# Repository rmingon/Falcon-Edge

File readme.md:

# FALCON-EDGE — An Open-Source Flying-Wing with an ESP32 Flight Computer

This repository contains hardware designs, documentation, and code for an aircraft project.

### New light version 400g instead of 800g

Falcon-Edge is a compact flying-wing airframe with a custom **ESP32-based flight computer**.  
This repo contains the **KiCad hardware project** and **3D CAD** needed to print, assemble, and fly your own Falcon-Edge.

---

## Highlights

- **Airframe**

  - 3D-printable center pod with **top and bottom service hatches** for fast access.
  - Designed for clean airflow over the pod; embedded antenna keep-out zone.
  - Uses off-the-shelf wing cores/foam or your own prints.

- **Avionics (KiCad)**
  - **ESP32-WROOM** module as the main controller (Wi-Fi/BLE for ground testing & logs).
  - **IMU:** MPU-6050 6-axis.
  - **Baro:** BMP280.
  - **GNSS header** for a u-blox NEO-style GPS module.
  - **Power:** AMS1117 regulators (3V3/5V) and dedicated servo power planes/decoupling.
  - **Programming:** UART header with EN/BOOT auto-reset circuitry.
  - **RF/Telemetry:** LoRa with edge SMA/U.FL footprint for an external antenna.

> See the schematic for exact pin mapping and connector naming.

---

## 📂 Repository Layout

hardware/ # KiCad project (.kicad_pro, .kicad_pcb, .kicad_sch, etc.)
cad/ # 3D parts for the center pod, hatches, and mounting (STLs/STEP)
images/ # Renders and board views used in this README (optional)

(If you keep everything at the repo root, this README references the images there by filename.)

---

## 🛠️ Getting Started

### 1) Hardware (KiCad)

- Open with **KiCad 8.x** or newer.
- Files:
  - `hardware.kicad_pro` – project
  - `hardware.kicad_sch` – schematic
  - `hardware.kicad_pcb` – PCB layout
- Generate Gerbers/BoM as usual and order from your preferred fab.

**Board preview**

**Schematic overview**

### 2) Print & Fit the Pod

- Recommended: **PETG** or **ABS** for the pod & hatches (heat-tolerant in the sun).
- Use heat-set **M3 inserts** for the hatch screws and board standoffs.
- Verify antenna **keep-out** in the pod before final mounting.

**Top hatch opening**

**Bottom hatch opening**

### 3) Wiring (at a glance)

- **Battery in** → power/battery header near regulators.
- **GPS** → dedicated UART header / GPS footprint.
- **Programming** → UART (EN/BOOT accessible).
- **Telemetry/Radio** → SMA/U.FL at the board edge.

> Exact connector names/positions: see the KiCad schematic & silkscreen.

---

## 📸 Gallery

**3D view of the board**

**Airframe with pod & hatches**

---

## 📏 Design Notes & Decisions

- **ESP32** was chosen for its strong dev-tooling and built-in wireless (great for bench testing/logging).
- **I²C sensor stack** (MPU-6050 + BMP280) keeps routing simple and expandable.
- **PCA9685** provides plenty of PWM channels beyond the two elevons (landing gear, camera gimbal, accessories).
- **Serviceability first:** both hatches allow quick access to battery, connectors, and the main board.

---

## 🗺️ Roadmap

- Flight firmware & mixer (stabilization, RTL, waypointing).
- Airspeed/Pitot and magnetometer options.
- On-board logging (SPI flash / SD).
- CAN/Telemetry radio module footprints.
- STL release of wing cores/center pod variants.

---

## 🤝 Contributing

PRs and issues are welcome:

- Hardware changes: update the KiCad files and include board screenshots.
- CAD tweaks: include STEP/STL and a short note on print settings.
- Please attach images when reporting fit or routing problems.

---

## License Overview

- **Hardware (schematics, PCB, CAD, design files):** CERN-OHL-S-2.0 (see `LICENSE-hardware`)
- **Documentation, images, drawings, renders:** CC BY 4.0 (see `LICENSE-docs`)
- **Software / firmware / scripts:** Apache 2.0 (see `LICENSE-code`)

## Attribution Requirement

If you use, modify, or redistribute any part of this project, you **must** give credit as follows:

> Based on FalconEgde by Rmingon (https://github.com/rmingon/Falcon-Edge) — Licensed under the corresponding license.

See `NOTICE` for full details.

---

## 🙏 Credits

Designed and built by **RMINGON**.

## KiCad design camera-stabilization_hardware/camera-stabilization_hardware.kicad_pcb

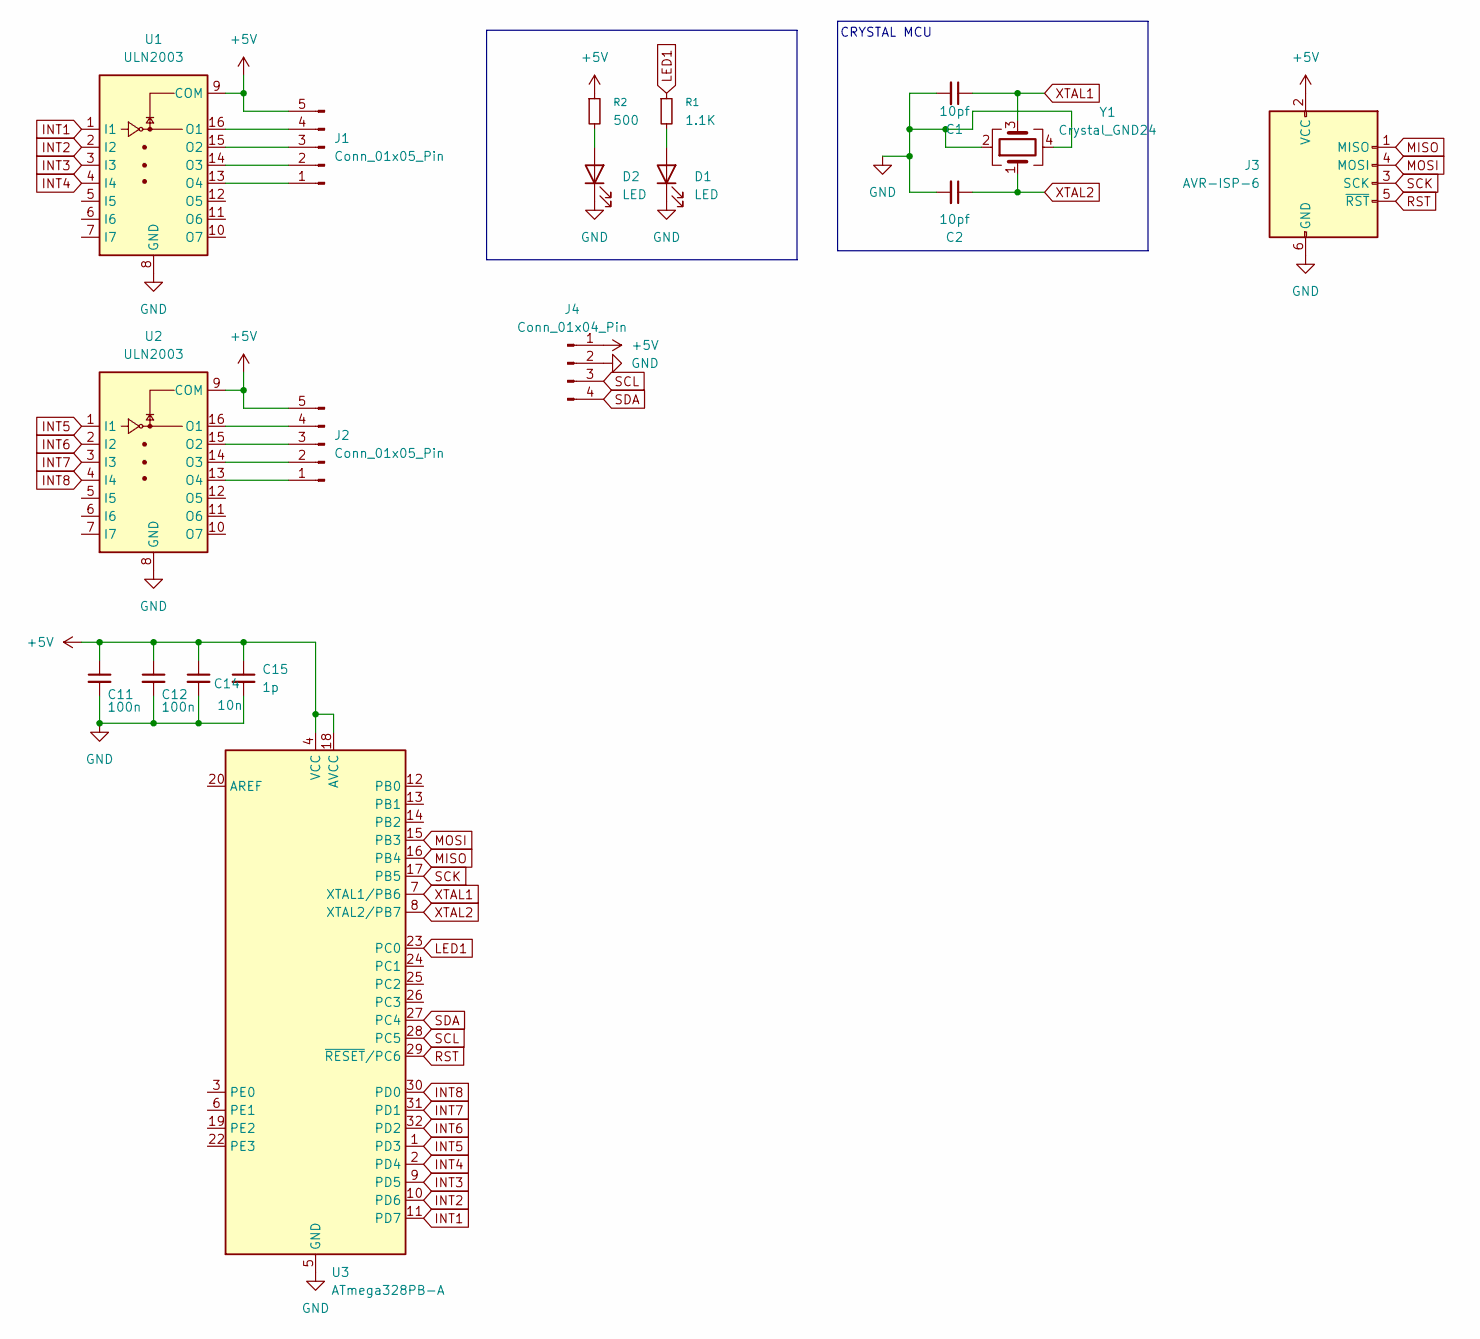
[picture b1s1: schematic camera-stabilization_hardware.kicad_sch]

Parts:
C1, C2: 10pf; C_0603_1608Metric; LCSC C106245
C11, C12: 100n; C_0603_1608Metric
C14: 10n; C_0603_1608Metric
C15: 1p; C_0603_1608Metric
D1, D2: LED; LED_0603_1608Metric
J1, J2: Conn_01x05_Pin; JST_XH_B5B-XH-A_1x05_P2.50mm_Vertical
J3: AVR-ISP-6; PinHeader_2x03_P2.54mm_Vertical
J4: Conn_01x04_Pin; JST_SH_BM04B-SRSS-TB_1x04-1MP_P1.00mm_Vertical
R1: 1.1K; R_0603_1608Metric
R2: 500; R_0603_1608Metric
U1, U2: ULN2003; SOIC-16_3.9x9.9mm_P1.27mm
U3: ATmega328PB-A; TQFP-32_7x7mm_P0.8mm
Y1: Crystal_GND24; Crystal_SMD_3225-4Pin_3.2x2.5mm

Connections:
+5V: C11.1, C12.1, C14.1, C15.1, J1.5, J2.5, J3.2 (VCC), J4.1, R2.1, U1.9 (COM), U2.9 (COM), U3.4 (VCC), U3.18 (AVCC)
GND: C1.2, C2.2, C11.2, C12.2, C14.2, C15.2, D1.1 (K), D2.1 (K), J3.6 (GND), J4.2, U1.8 (GND), U2.8 (GND), U3.5 (GND), U3.21 (GND), Y1.2, Y1.4
INT1: U1.1 (I1), U3.11 (PD7)
INT2: U1.2 (I2), U3.10 (PD6)
INT3: U1.3 (I3), U3.9 (PD5)
INT4: U1.4 (I4), U3.2 (PD4)
INT5: U2.1 (I1), U3.1 (PD3)
INT6: U2.2 (I2), U3.32 (PD2)
INT7: U2.3 (I3), U3.31 (PD1)
INT8: U2.4 (I4), U3.30 (PD0)
LED1: R1.1, U3.23 (PC0)
MISO: J3.1 (MISO), U3.16 (PB4)
MOSI: J3.4 (MOSI), U3.15 (PB3)
unnamed: D1.2 (A), R1.2
unnamed: D2.2 (A), R2.2
unnamed: J1.1, U1.13 (O4)
unnamed: J1.2, U1.14 (O3)
unnamed: J1.3, U1.15 (O2)
unnamed: J1.4, U1.16 (O1)
unnamed: J2.1, U2.13 (O4)
unnamed: J2.2, U2.14 (O3)
unnamed: J2.3, U2.15 (O2)
unnamed: J2.4, U2.16 (O1)
RST: J3.5 (~RST), U3.29 (~RESET/PC6)
SCK: J3.3 (SCK), U3.17 (PB5)
SCL: J4.3, U3.28 (PC5)
SDA: J4.4, U3.27 (PC4)
XTAL1: C1.1, U3.7 (XTAL1/PB6), Y1.3
XTAL2: C2.1, U3.8 (XTAL2/PB7), Y1.1

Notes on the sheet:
CRYSTAL MCU

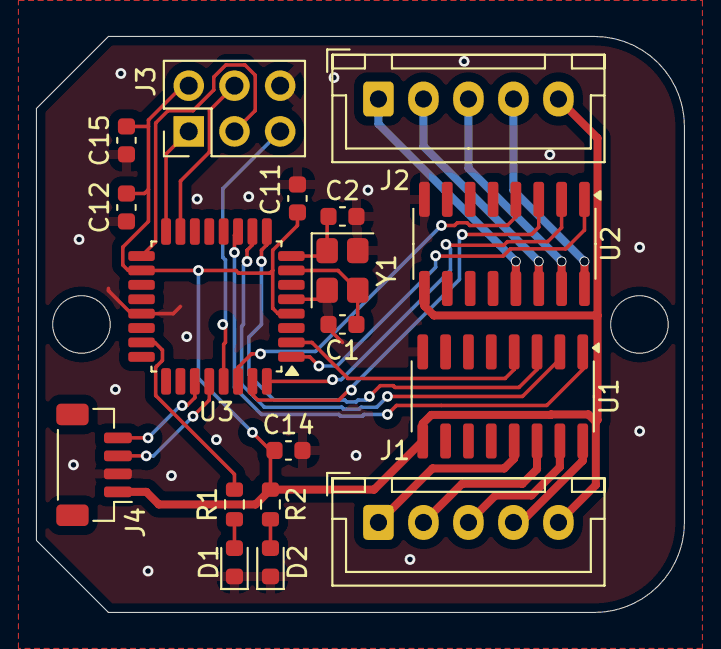
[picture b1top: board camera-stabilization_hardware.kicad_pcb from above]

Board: 2 copper layers, 36.0 x 32.0 mm, 18 parts (0 on the bottom side), 29 nets.

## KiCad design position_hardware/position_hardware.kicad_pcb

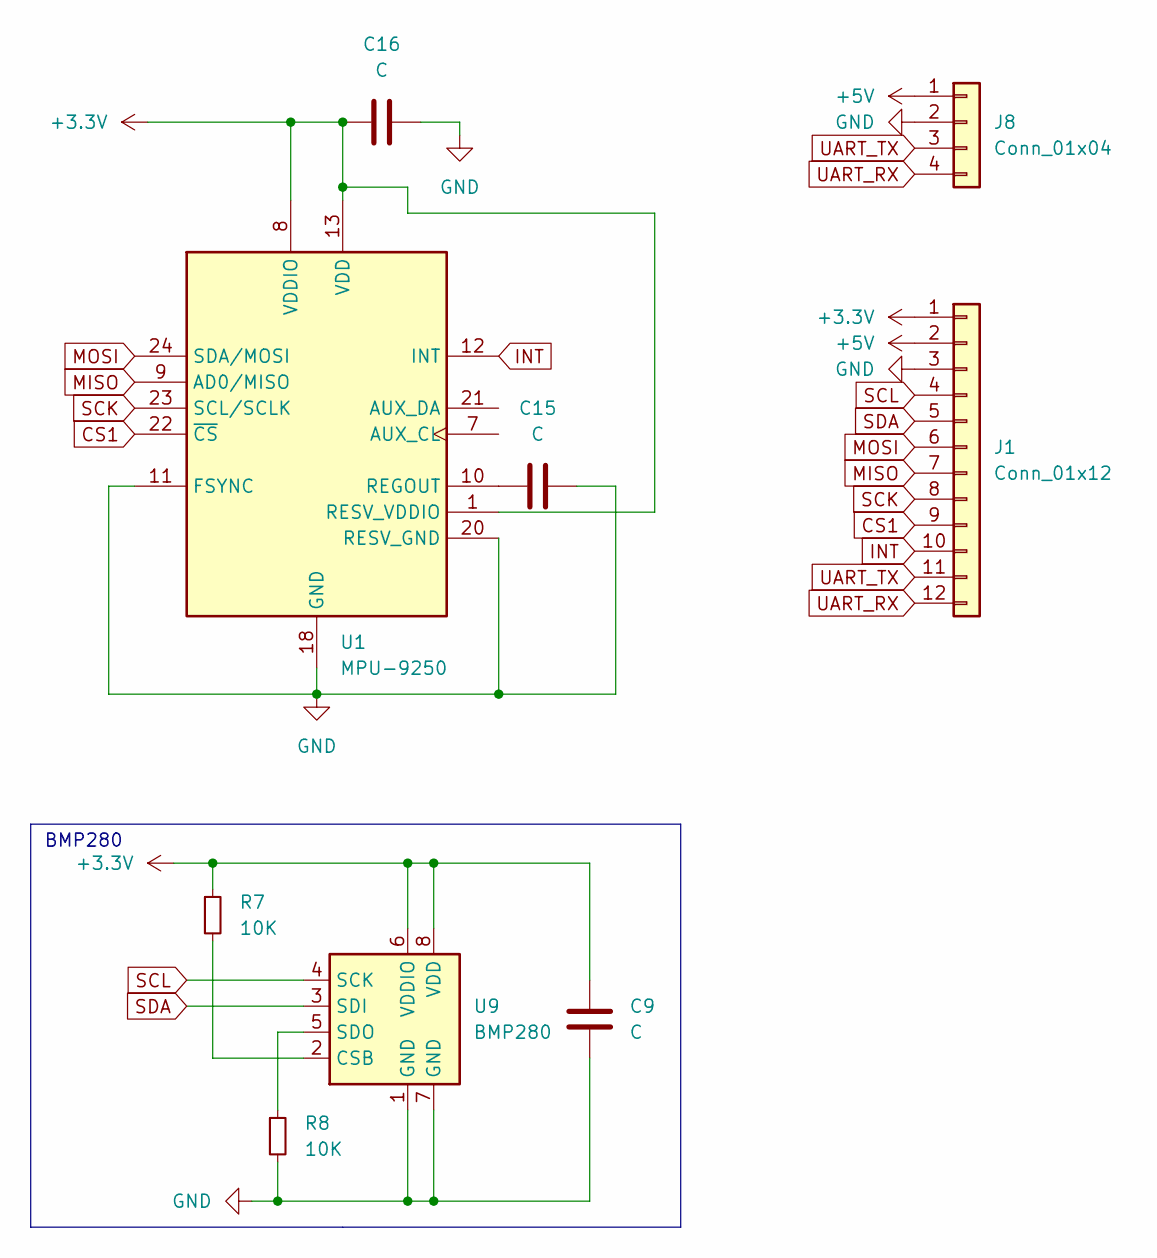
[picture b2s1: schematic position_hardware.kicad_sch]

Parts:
C9, C15, C16: C; C_0603_1608Metric
J1: Conn_01x12
J8: Conn_01x04; PinHeader_1x04_P2.54mm_Vertical
R7, R8: 10K; R_0603_1608Metric
U1: MPU-9250; InvenSense_QFN-24_3x3mm_P0.4mm
U9: BMP280; Bosch_LGA-8_2x2.5mm_P0.65mm_ClockwisePinNumbering

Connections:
+3.3V: C9.1, C16.1, J1.1, R7.1, U1.1 (RESV_VDDIO), U1.8 (VDDIO), U1.13 (VDD), U9.6 (VDDIO), U9.8 (VDD)
+5V: J1.2, J8.1
CS1: J1.9, U1.22 (~CS)
GND: C9.2, C15.2, C16.2, J1.3, J8.2, R8.2, U1.11 (FSYNC), U1.18 (GND), U1.20 (RESV_GND), U9.1 (GND), U9.7 (GND)
INT: J1.10, U1.12 (INT)
MISO: J1.7, U1.9 (AD0/MISO)
MOSI: J1.6, U1.24 (SDA/MOSI)
unnamed: C15.1, U1.10 (REGOUT)
unnamed: R7.2, U9.2 (CSB)
unnamed: R8.1, U9.5 (SDO)
SCK: J1.8, U1.23 (SCL/SCLK)
SCL: J1.4, U9.4 (SCK)
SDA: J1.5, U9.3 (SDI)
UART_RX: J1.12, J8.4
UART_TX: J1.11, J8.3

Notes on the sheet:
BMP280

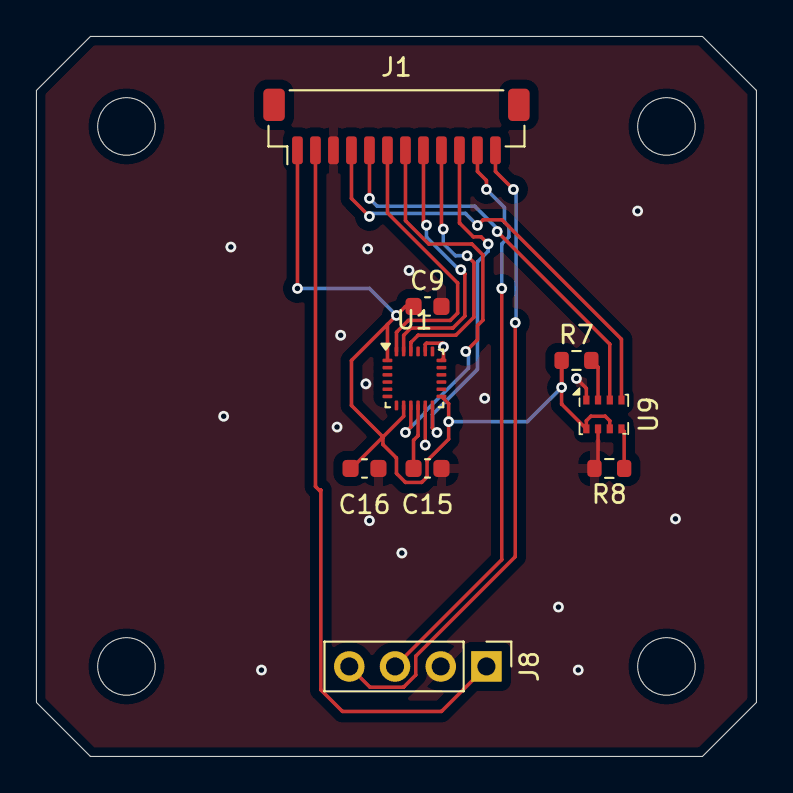
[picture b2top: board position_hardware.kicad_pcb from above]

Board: 2 copper layers, 40.0 x 40.0 mm, 9 parts (0 on the bottom side), 15 nets.

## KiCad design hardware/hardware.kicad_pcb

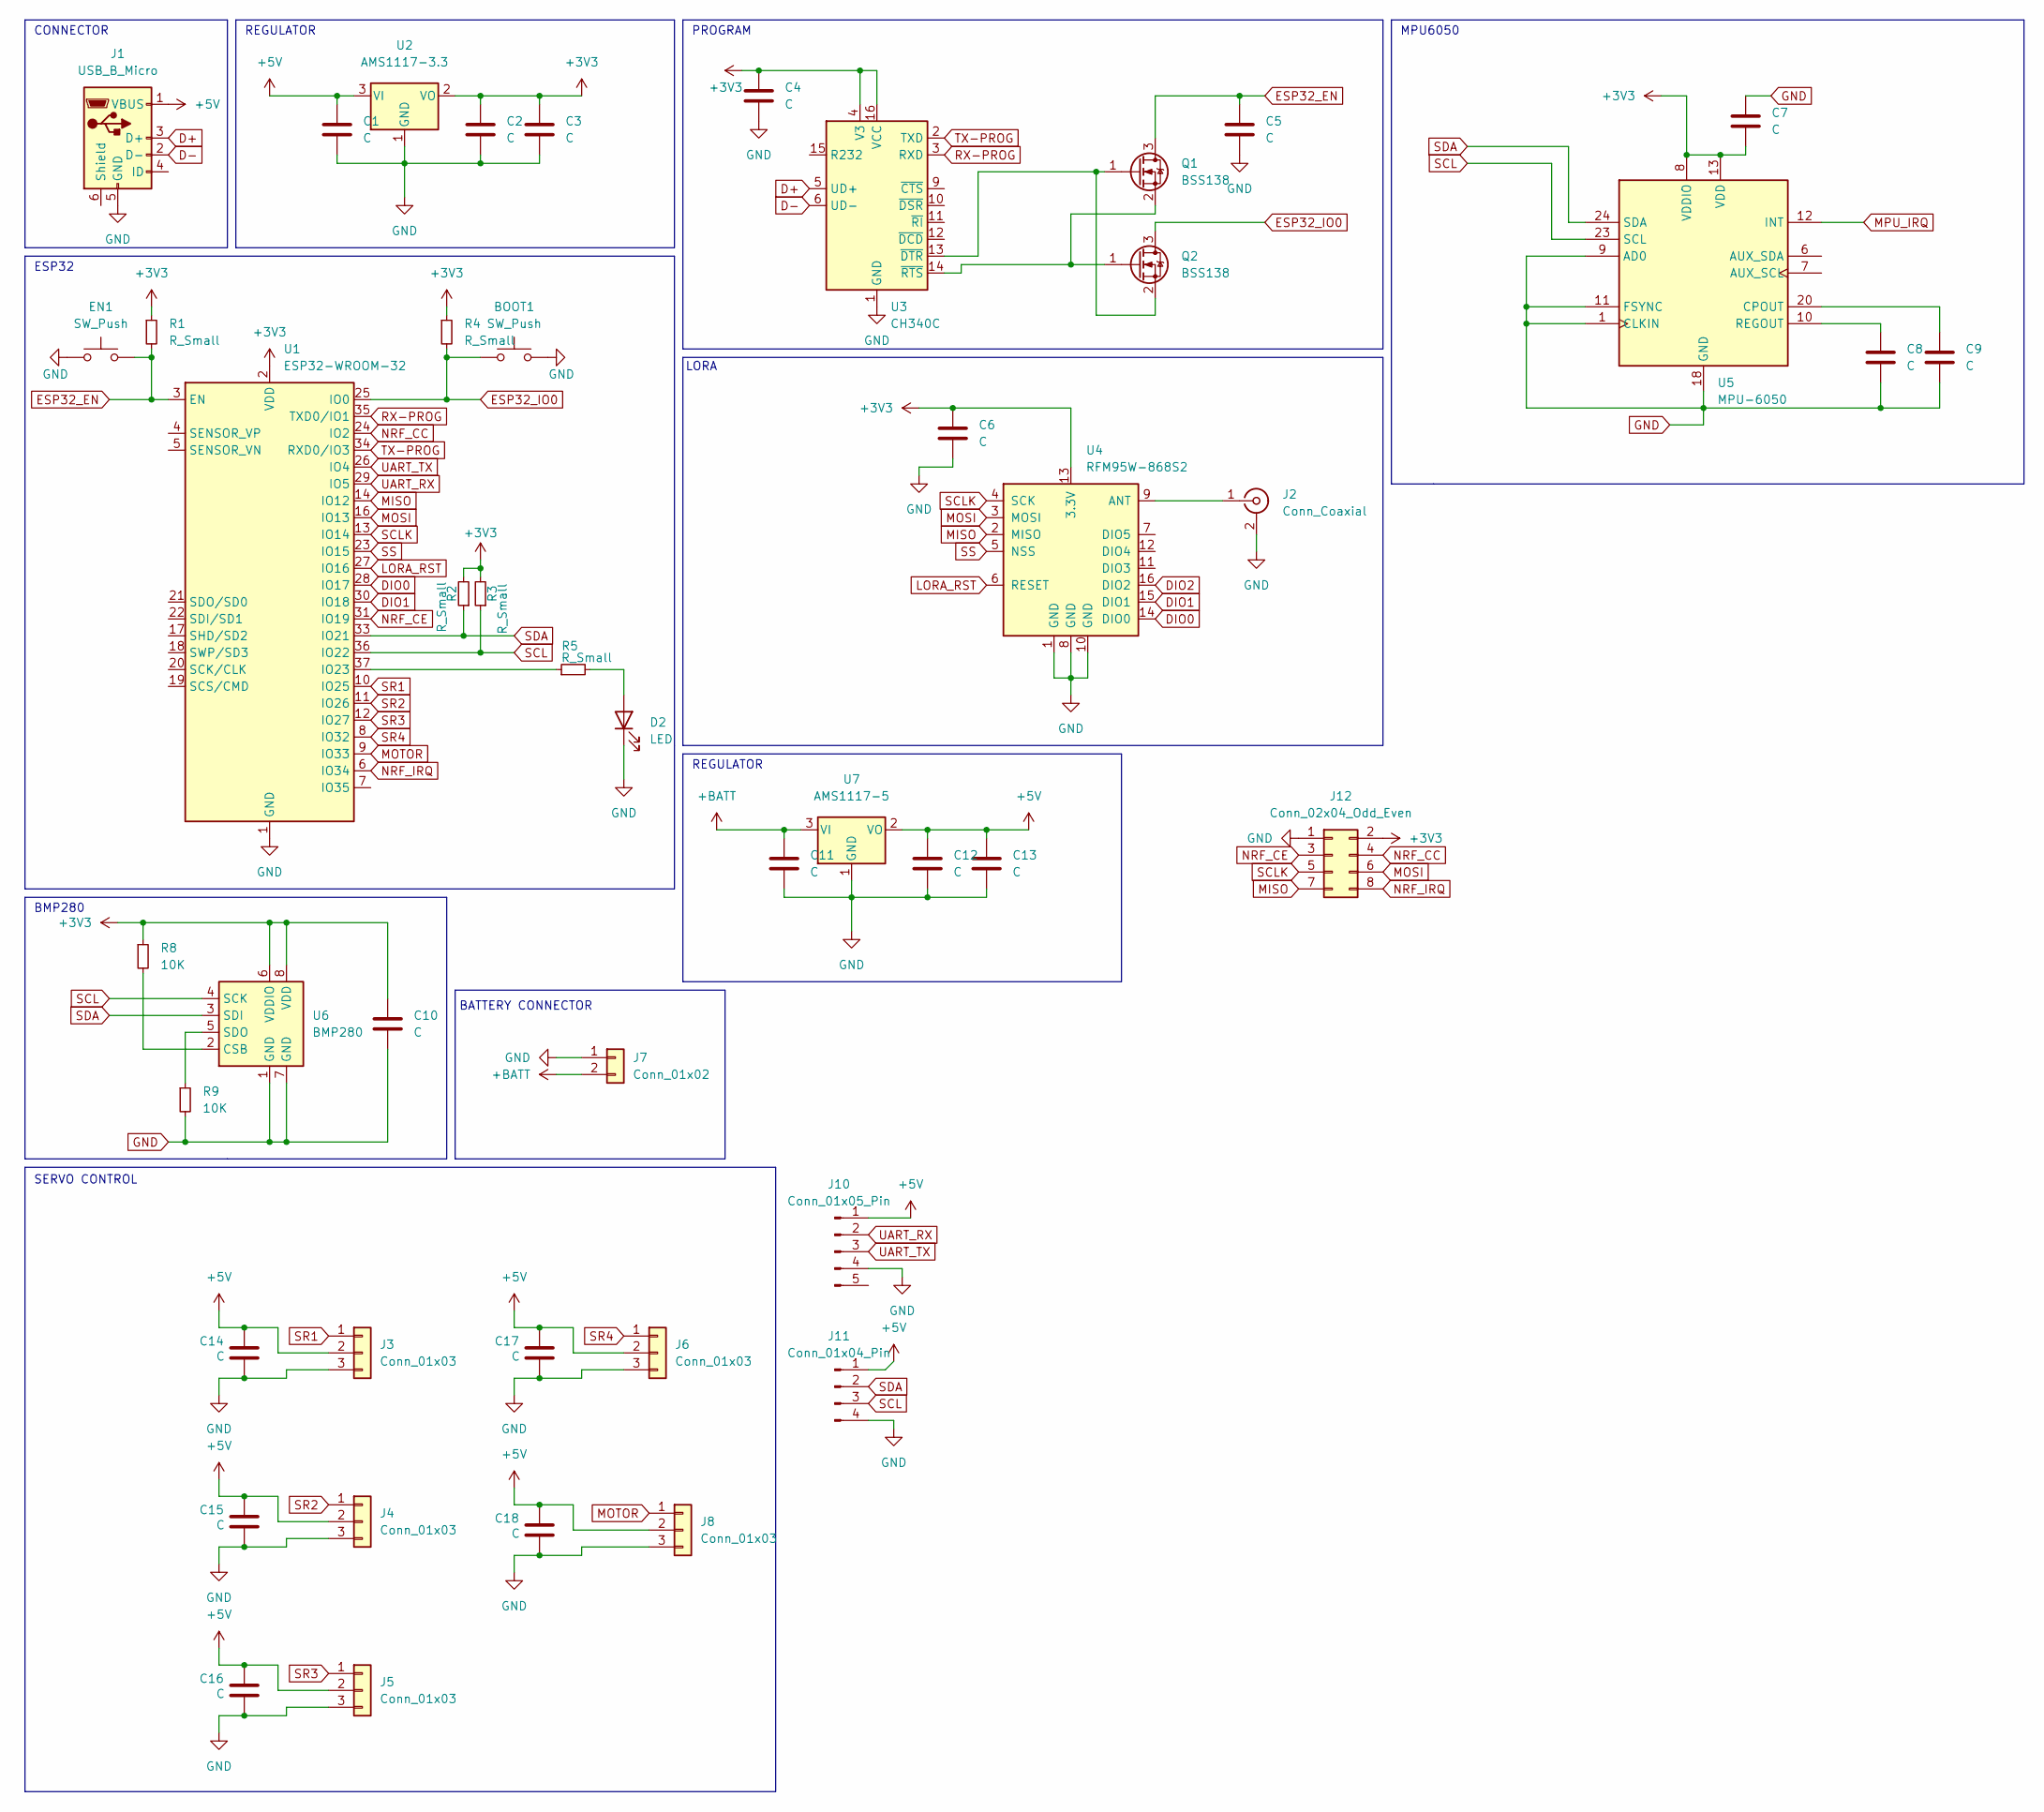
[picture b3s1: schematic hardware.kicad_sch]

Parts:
BOOT1: SW_Push; SW_SPST_FSMSM
C1, C2, C3, C4, C5, C6, C7, C8, C9, C10, C11, C12, C13, C14, C15, C16, C17, C18: C; C_0603_1608Metric
D2: LED; LED_0603_1608Metric
EN1: SW_Push; SW_SPST_FSMSM
J1: USB_B_Micro; USB_Micro-B_Amphenol_10118194_Horizontal
J2: Conn_Coaxial; SMA_Samtec_SMA-J-P-H-ST-EM1_EdgeMount
J3, J4, J5, J6, J8: Conn_01x03; PinHeader_1x03_P2.54mm_Vertical
J7: Conn_01x02; AMASS_XT30U-F_1x02_P5.0mm_Vertical
J10: Conn_01x05_Pin; PinHeader_1x05_P2.54mm_Vertical
J11: Conn_01x04_Pin; PinHeader_1x04_P2.54mm_Vertical
J12: Conn_02x04_Odd_Even; PinHeader_2x04_P2.54mm_Vertical
Q1, Q2: BSS138; SOT-23
R1, R2, R3, R4, R5: R_Small; R_0603_1608Metric
R8, R9: 10K; R_0603_1608Metric
U1: ESP32-WROOM-32
U2: AMS1117-3.3; SOT-223-3_TabPin2
U3: CH340C; SOIC-16_3.9x9.9mm_P1.27mm
U4: RFM95W-868S2; HOPERF_RFM9XW_SMD
U5: MPU-6050; InvenSense_QFN-24_4x4mm_P0.5mm
U6: BMP280; Bosch_LGA-8_2x2.5mm_P0.65mm_ClockwisePinNumbering
U7: AMS1117-5; SOT-223-3_TabPin2

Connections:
+3V3: C2.1, C3.1, C4.1, C6.1, C7.2, C10.1, J12.2, R1.1, R2.2, R3.2, R4.1, R8.1, U1.2 (VDD), U2.2 (VO), U3.4 (V3), U3.16 (VCC), U4.13 (3.3V), U5.8 (VDDIO), U5.13 (VDD), U6.6 (VDDIO), U6.8 (VDD)
+5V: C1.1, C12.1, C13.1, C14.1, C15.1, C16.1, C17.1, C18.1, J1.1 (VBUS), J3.2, J4.2, J5.2, J6.2, J8.2, J10.1, J11.1, U2.3 (VI), U7.2 (VO)
+BATT: C11.1, J7.2, U7.3 (VI)
D+: J1.3 (D+), U3.5 (UD+)
D-: J1.2 (D-), U3.6 (UD-)
DIO0: U1.28 (IO17), U4.14 (DIO0)
DIO1: U1.30 (IO18), U4.15 (DIO1)
DIO2: U4.16 (DIO2)
ESP32_EN: C5.1, EN1.2, Q1.3 (D), R1.2, U1.3 (EN)
ESP32_IO0: BOOT1.1, Q2.3 (D), R4.2, U1.25 (IO0)
GND: BOOT1.2, C1.2, C2.2, C3.2, C4.2, C5.2, C6.2, C7.1, C8.2, C9.2, C10.2, C11.2, C12.2, C13.2, C14.2, C15.2, C16.2, C17.2, C18.2, D2.1 (K), EN1.1, J1.5 (GND), J2.2 (Ext), J3.3, J4.3, J5.3, J6.3, J7.1, J8.3, J10.4, J11.4, J12.1, R9.2, U1.1 (GND), U1.15 (GND), U1.38 (GND), U1.39 (GND), U2.1 (GND), U3.1 (GND), U4.1 (GND), U4.8 (GND), U4.10 (GND), U5.1 (CLKIN), U5.9 (AD0), U5.11 (FSYNC), U5.18 (GND), U6.1 (GND), U6.7 (GND), U7.1 (GND)
LORA_RST: U1.27 (IO16), U4.6 (RESET)
MISO: J12.7, U1.14 (IO12), U4.2 (MISO)
MOSI: J12.6, U1.16 (IO13), U4.3 (MOSI)
MOTOR: J8.1, U1.9 (IO33)
MPU_IRQ: U5.12 (INT)
NRF_CC: J12.4, U1.24 (IO2)
NRF_CE: J12.3, U1.31 (IO19)
NRF_IRQ: J12.8, U1.6 (IO34)
unnamed: D2.2 (A), R5.2
unnamed: J2.1 (In), U4.9 (ANT)
unnamed: Q1.1 (G), Q2.2 (S), U3.13 (~DTR)
unnamed: Q1.2 (S), Q2.1 (G), U3.14 (~RTS)
unnamed: R5.1, U1.37 (IO23)
unnamed: C9.1, U5.20 (CPOUT)
unnamed: C8.1, U5.10 (REGOUT)
unnamed: R8.2, U6.2 (CSB)
unnamed: R9.1, U6.5 (SDO)
RX-PROG: U1.35 (TXD0/IO1), U3.3 (RXD)
SCL: J11.3, R3.1, U1.36 (IO22), U5.23 (SCL), U6.4 (SCK)
SCLK: J12.5, U1.13 (IO14), U4.4 (SCK)
SDA: J11.2, R2.1, U1.33 (IO21), U5.24 (SDA), U6.3 (SDI)
SR1: J3.1, U1.10 (IO25)
SR2: J4.1, U1.11 (IO26)
SR3: J5.1, U1.12 (IO27)
SR4: J6.1, U1.8 (IO32)
SS: U1.23 (IO15), U4.5 (NSS)
TX-PROG: U1.34 (RXD0/IO3), U3.2 (TXD)
UART_RX: J10.2, U1.29 (IO5)
UART_TX: J10.3, U1.26 (IO4)

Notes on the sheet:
ESP32
BMP280
MPU6050
SERVO CONTROL
REGULATOR
LORA
CONNECTOR
BATTERY CONNECTOR
PROGRAM

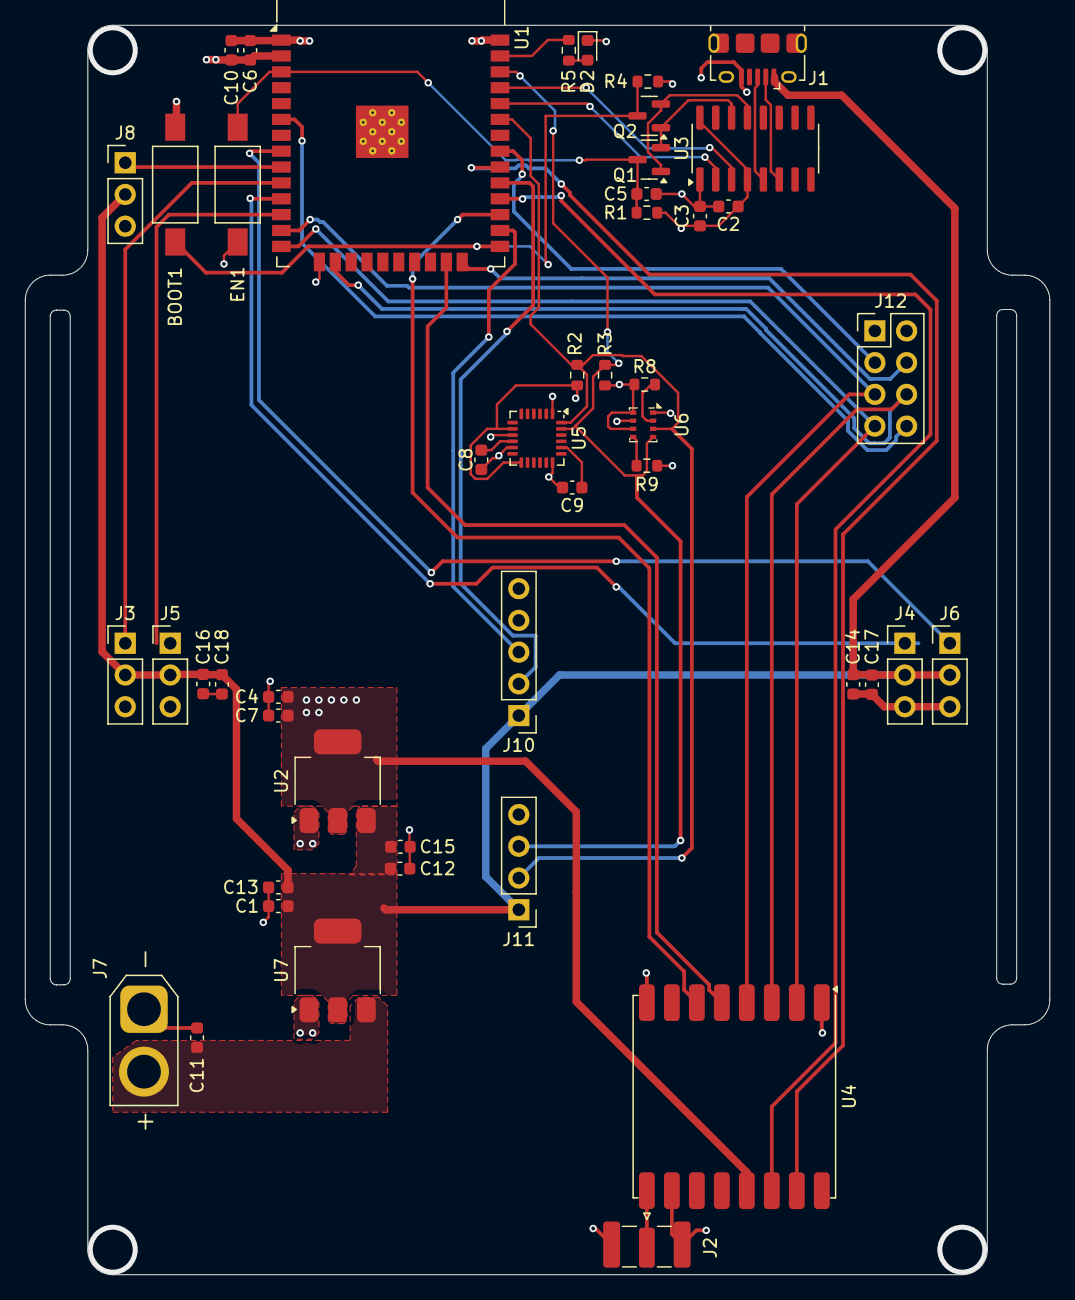
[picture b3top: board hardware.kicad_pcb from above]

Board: 4 copper layers, 82.0 x 100.0 mm, 48 parts (0 on the bottom side), 38 nets.

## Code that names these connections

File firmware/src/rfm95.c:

#include "rfm95.h"
#include "config.h"
#include "esp_log.h"
#include "freertos/FreeRTOS.h"
#include "freertos/task.h"

static const char *TAG = "RFM95";

static esp_err_t rfm95_write_reg(rfm95_t *dev, uint8_t reg, uint8_t value)
{
    uint8_t tx_data[2] = {reg | 0x80, value}; // Set write bit
    spi_transaction_t trans = {
        .length = 16,
        .tx_buffer = tx_data,
    };
    return spi_device_transmit(dev->spi, &trans);
}

static esp_err_t rfm95_read_reg(rfm95_t *dev, uint8_t reg, uint8_t *value)
{
    uint8_t tx_data[2] = {reg & 0x7F, 0x00}; // Clear write bit
    uint8_t rx_data[2];
    spi_transaction_t trans = {
        .length = 16,
        .tx_buffer = tx_data,
        .rx_buffer = rx_data,
    };
    esp_err_t ret = spi_device_transmit(dev->spi, &trans);
    if (ret == ESP_OK) {
        *value = rx_data[1];
    }
    return ret;
}

static esp_err_t rfm95_set_mode(rfm95_t *dev, uint8_t mode)
{
    return rfm95_write_reg(dev, RFM95_REG_OP_MODE, RFM95_LONG_RANGE_MODE | mode);
}

esp_err_t rfm95_init(rfm95_t *dev, spi_host_device_t spi_host, uint32_t frequency)
{
    dev->cs_pin = SPI_SS_PIN;
    dev->rst_pin = LORA_RST_PIN;
    dev->dio0_pin = LORA_DIO0_PIN;
    dev->dio1_pin = LORA_DIO1_PIN;
    dev->frequency = frequency;

    // Configure reset pin
    gpio_config_t io_conf = {
        .pin_bit_mask = (1ULL << dev->rst_pin),
        .mode = GPIO_MODE_OUTPUT,
        .pull_up_en = GPIO_PULLUP_DISABLE,
        .pull_down_en = GPIO_PULLDOWN_DISABLE,
        .intr_type = GPIO_INTR_DISABLE,
    };
    gpio_config(&io_conf);

    // Configure DIO pins as inputs
    io_conf.pin_bit_mask = (1ULL << dev->dio0_pin) | (1ULL << dev->dio1_pin);
    io_conf.mode = GPIO_MODE_INPUT;
    gpio_config(&io_conf);

    // Reset RFM95
    gpio_set_level(dev->rst_pin, 0);
    vTaskDelay(pdMS_TO_TICKS(10));
    gpio_set_level(dev->rst_pin, 1);
    vTaskDelay(pdMS_TO_TICKS(10));

    // Configure SPI
    spi_bus_config_t buscfg = {
        .miso_io_num = SPI_MISO_PIN,
        .mosi_io_num = SPI_MOSI_PIN,
        .sclk_io_num = SPI_SCK_PIN,
        .quadwp_io_num = -1,
        .quadhd_io_num = -1,
        .max_transfer_sz = 256,
    };

    esp_err_t ret = spi_bus_initialize(spi_host, &buscfg, SPI_DMA_CH_AUTO);
    if (ret != ESP_OK && ret != ESP_ERR_INVALID_STATE) {
        ESP_LOGE(TAG, "Failed to initialize SPI bus");
        return ret;
    }

    spi_device_interface_config_t devcfg = {
        .clock_speed_hz = 1000000,  // 1 MHz
        .mode = 0,
        .spics_io_num = dev->cs_pin,
        .queue_size = 7,
    };

    ret = spi_bus_add_device(spi_host, &devcfg, &dev->spi);
    if (ret != ESP_OK) {
        ESP_LOGE(TAG, "Failed to add SPI device");
        return ret;
    }

    // Check version
    uint8_t version;
    ret = rfm95_read_reg(dev, RFM95_REG_VERSION, &version);
    if (ret != ESP_OK) {
        ESP_LOGE(TAG, "Failed to read version register");
        return ret;
    }

    if (version != 0x12) {
        ESP_LOGE(TAG, "Invalid version: 0x%02X (expected 0x12)", version);
        return ESP_ERR_NOT_FOUND;
    }

    ESP_LOGI(TAG, "RFM95 detected, version: 0x%02X", version);

    // Set sleep mode
    rfm95_set_mode(dev, RFM95_MODE_SLEEP);
    vTaskDelay(pdMS_TO_TICKS(10));

    // Set frequency
    uint64_t frf = ((uint64_t)frequency << 19) / 32000000;
    rfm95_write_reg(dev, RFM95_REG_FRF_MSB, (uint8_t)(frf >> 16));
    rfm95_write_reg(dev, RFM95_REG_FRF_MID, (uint8_t)(frf >> 8));
    rfm95_write_reg(dev, RFM95_REG_FRF_LSB, (uint8_t)(frf >> 0));

    // Set FIFO base addresses
    rfm95_write_reg(dev, RFM95_REG_FIFO_TX_BASE_ADDR, 0x00);
    rfm95_write_reg(dev, RFM95_REG_FIFO_RX_BASE_ADDR, 0x00);

    // Set LNA boost
    rfm95_write_reg(dev, 0x0C, 0x23);

    // Set auto AGC
    rfm95_write_reg(dev, RFM95_REG_MODEM_CONFIG_3, 0x04);

    // Set default configuration (BW=125kHz, CR=4/5, SF=7)
    rfm95_write_reg(dev, RFM95_REG_MODEM_CONFIG_1, 0x72);
    rfm95_write_reg(dev, RFM95_REG_MODEM_CONFIG_2, 0x74);

    // Set preamble length
    rfm95_write_reg(dev, RFM95_REG_PREAMBLE_MSB, 0x00);
    rfm95_write_reg(dev, RFM95_REG_PREAMBLE_LSB, 0x08);

    // Set TX power to 17 dBm
    rfm95_set_tx_power(dev, 17);

    // Set standby mode
    rfm95_set_mode(dev, RFM95_MODE_STDBY);

    ESP_LOGI(TAG, "RFM95 initialized at %.1f MHz", frequency / 1000000.0f);
    return ESP_OK;
}

esp_err_t rfm95_set_tx_power(rfm95_t *dev, int8_t power)
{
    if (power < 5) power = 5;
    if (power > 23) power = 23;

    if (power > 20) {
        // High power +20 dBm operation
        rfm95_write_reg(dev, RFM95_REG_PA_DAC, 0x87);
        power -= 3;
    } else {
        rfm95_write_reg(dev, RFM95_REG_PA_DAC, 0x84);
    }

    // PA_BOOST pin, max power
    uint8_t pa_config = 0x80 | (power - 5);
    return rfm95_write_reg(dev, RFM95_REG_PA_CONFIG, pa_config);
}

esp_err_t rfm95_send(rfm95_t *dev, const uint8_t *data, uint8_t len)
{
    if (len > RFM95_MAX_PAYLOAD) {
        ESP_LOGE(TAG, "Payload too large: %d bytes", len);
        return ESP_ERR_INVALID_SIZE;
    }

    // Set standby mode
    rfm95_set_mode(dev, RFM95_MODE_STDBY);

    // Set FIFO pointer to TX base
    rfm95_write_reg(dev, RFM95_REG_FIFO_ADDR_PTR, 0x00);

    // Write data to FIFO
    for (int i = 0; i < len; i++) {
        rfm95_write_reg(dev, RFM95_REG_FIFO, data[i]);
    }

    // Set payload length
    rfm95_write_reg(dev, RFM95_REG_PAYLOAD_LENGTH, len);

    // Start transmission
    rfm95_set_mode(dev, RFM95_MODE_TX);

    // Wait for TX done (DIO0)
    uint32_t start = xTaskGetTickCount();
    while (gpio_get_level(dev->dio0_pin) == 0) {
        if ((xTaskGetTickCount() - start) > pdMS_TO_TICKS(1000)) {
            ESP_LOGE(TAG, "TX timeout");
            return ESP_ERR_TIMEOUT;
        }
        vTaskDelay(pdMS_TO_TICKS(1));
    }

    // Clear IRQ flags
    rfm95_write_reg(dev, RFM95_REG_IRQ_FLAGS, 0xFF);

    // Set standby mode
    rfm95_set_mode(dev, RFM95_MODE_STDBY);

    ESP_LOGI(TAG, "Sent %d bytes", len);
    return ESP_OK;
}

int rfm95_receive(rfm95_t *dev, uint8_t *data, uint8_t len, uint32_t timeout_ms)
{
    // Set RX continuous mode
    rfm95_set_mode(dev, RFM95_MODE_RX_CONTINUOUS);

    // Wait for RX done (DIO0)
    uint32_t start = xTaskGetTickCount();
    while (gpio_get_level(dev->dio0_pin) == 0) {
        if ((xTaskGetTickCount() - start) > pdMS_TO_TICKS(timeout_ms)) {
            rfm95_set_mode(dev, RFM95_MODE_STDBY);
            return 0; // Timeout, no data received
        }
        vTaskDelay(pdMS_TO_TICKS(1));
    }

    // Read IRQ flags
    uint8_t irq_flags;
    rfm95_read_reg(dev, RFM95_REG_IRQ_FLAGS, &irq_flags);

    // Clear IRQ flags
    rfm95_write_reg(dev, RFM95_REG_IRQ_FLAGS, 0xFF);

    // Check if RX done
    if (irq_flags & RFM95_IRQ_RX_DONE) {
        // Read received length
        uint8_t rx_len;
        rfm95_read_reg(dev, RFM95_REG_RX_NB_BYTES, &rx_len);

        if (rx_len > len) {
            rx_len = len;
        }

        // Get FIFO RX current address
        uint8_t fifo_addr;
        rfm95_read_reg(dev, RFM95_REG_FIFO_RX_CURRENT_ADDR, &fifo_addr);

        // Set FIFO pointer
        rfm95_write_reg(dev, RFM95_REG_FIFO_ADDR_PTR, fifo_addr);

        // Read data from FIFO
        for (int i = 0; i < rx_len; i++) {
            rfm95_read_reg(dev, RFM95_REG_FIFO, &data[i]);
        }

        rfm95_set_mode(dev, RFM95_MODE_STDBY);
        ESP_LOGI(TAG, "Received %d bytes", rx_len);
        return rx_len;
    }

    rfm95_set_mode(dev, RFM95_MODE_STDBY);
    return 0;
}

int16_t rfm95_get_rssi(rfm95_t *dev)
{
    uint8_t rssi;
    rfm95_read_reg(dev, RFM95_REG_PKT_RSSI_VALUE, &rssi);
    return -157 + (int16_t)rssi;
}

esp_err_t rfm95_set_spreading_factor(rfm95_t *dev, uint8_t sf)
{
    if (sf < 6 || sf > 12) {
        return ESP_ERR_INVALID_ARG;
    }

    uint8_t config2;
    rfm95_read_reg(dev, RFM95_REG_MODEM_CONFIG_2, &config2);
    config2 = (config2 & 0x0F) | ((sf << 4) & 0xF0);
    return rfm95_write_reg(dev, RFM95_REG_MODEM_CONFIG_2, config2);
}

esp_err_t rfm95_set_bandwidth(rfm95_t *dev, uint8_t bw)
{
    if (bw > 9) {
        return ESP_ERR_INVALID_ARG;
    }

    uint8_t config1;
    rfm95_read_reg(dev, RFM95_REG_MODEM_CONFIG_1, &config1);
    config1 = (config1 & 0x0F) | (bw << 4);
    return rfm95_write_reg(dev, RFM95_REG_MODEM_CONFIG_1, config1);
}

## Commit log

2025-08-28 first commit pcb
2025-08-28 update wiring
2025-08-28 add battery fix
2025-08-28 add pictures
2025-08-28 add readme
2025-09-16 add light version
2025-09-21 add schematic position system
2025-09-21 position system hardware pcb
2025-10-01 add licences
2025-10-01 add gps module
2025-10-03 minimal schematic components
2025-10-03 added pcb wiring camera stabilization
2025-10-12 add firmware
2025-10-12 update bmp280 add
